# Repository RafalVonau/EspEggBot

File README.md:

# EggBot on ESP8266

## Info

This repository contains the software for my ESP8266 based EggBot.
An [EggBot](https://egg-bot.com/) is a machine for drawing on eggs. I built an eggbot from 3d printed parts from the [thingiverse](https://www.thingiverse.com/thing:3431363) website. 
I'm using an D1 mini(ESP8266) for controlling the steppers and the servo. 

The project is based on:
- [EggDuino](https://github.com/schlion/EggDuino) - some code ported to ESP8266
- [EggBot Inkscape plugin](http://wiki.evilmadscientist.com/Installing_software) - I modified the plugin to automatically detect the USB to UART converter present on the D1 mini board and in case it fails to detect the USB converter, try to connect via TCP with eggbot.local:2500 address
- [EggEsp](https://github.com/M4GNV5/EggEsp) - svg to gcode parser
- [SvgToGCode](https://github.com/evomotors/SvgToGCode) - svg to gcode parser

Features:
- Implemented Eggbot-Protocol-Version 2.1.0
- Turn-on homing: switch-on position of pen will be taken as reference point.
- No collision-detection!!
- Supported Servos: standard analog mini servos like TG9e, SG90, ES08MA, HXT900, etc.
- Taking svgs directly (over www) -> no need for external software.
- Inkscape plugin (commands over serial port or TCP socket on port 2500).

The test project was built on D1 mini board connected to PC computer over USB as /dev/ttyUSB0 under Linux.
Uncomment and modify Wifi client settings in secrets.h file:
* #define WIFI_SSID                "EggBot"
* #define WIFI_PASS                "EggBotPass"

# Parts needed:
* D1 mini (ESP8266),
* DC/DC converter 12V to 5V,
* DC/DC converter 5V to 3.3V,
* 2 x TMC2208/A4988/equivalent,
* 2 x Stepper mottor Nema 17
* Servo SG90/equivalent
* 3D printed and mechanical parts from [thingiverse](https://www.thingiverse.com/thing:3431363)
* wires
* connectors

# D1 mini CONNECTIONS
* STEP1(EGG)- GPIO14 (D5)
* DIR1(EGG) - GPIO13 (D7)
* STEP2(ARM)- GPIO5  (D1)
* DIR2(ARM) - GPIO4  (D2)
* MOTTOR EN - GPIO2  (D4)
* SERVO     - GPIO12 (D6)
* BUTTON    - GPIO0  (D3)

# Wiring

## Building

The project uses platformio build environment. 
[PlatformIO](https://platformio.org/) - Professional collaborative platform for embedded development.

* install PlatformIO
* enter project directory (esp8266_firmware)
* connect Webmos D1 mini board to PC computer over USB cable.
* type in terminal:
  platformio run -t upload

You can also use IDE to build this project on Linux/Windows/Mac. My fvorite ones:
* [Code](https://code.visualstudio.com/) 
* [Atom](https://atom.io/)

## Inkscape plugin installation

Installation:
1. Install inkscape version 0.94
2. Copy inkscape_plugin subdirectories to inkscape user folder:
* On Linux   (~/.config/inkscape/),
* On Windows (c:\Users\[UserName]\AppData\Roaming\inkscape\)

Enjoy :-)

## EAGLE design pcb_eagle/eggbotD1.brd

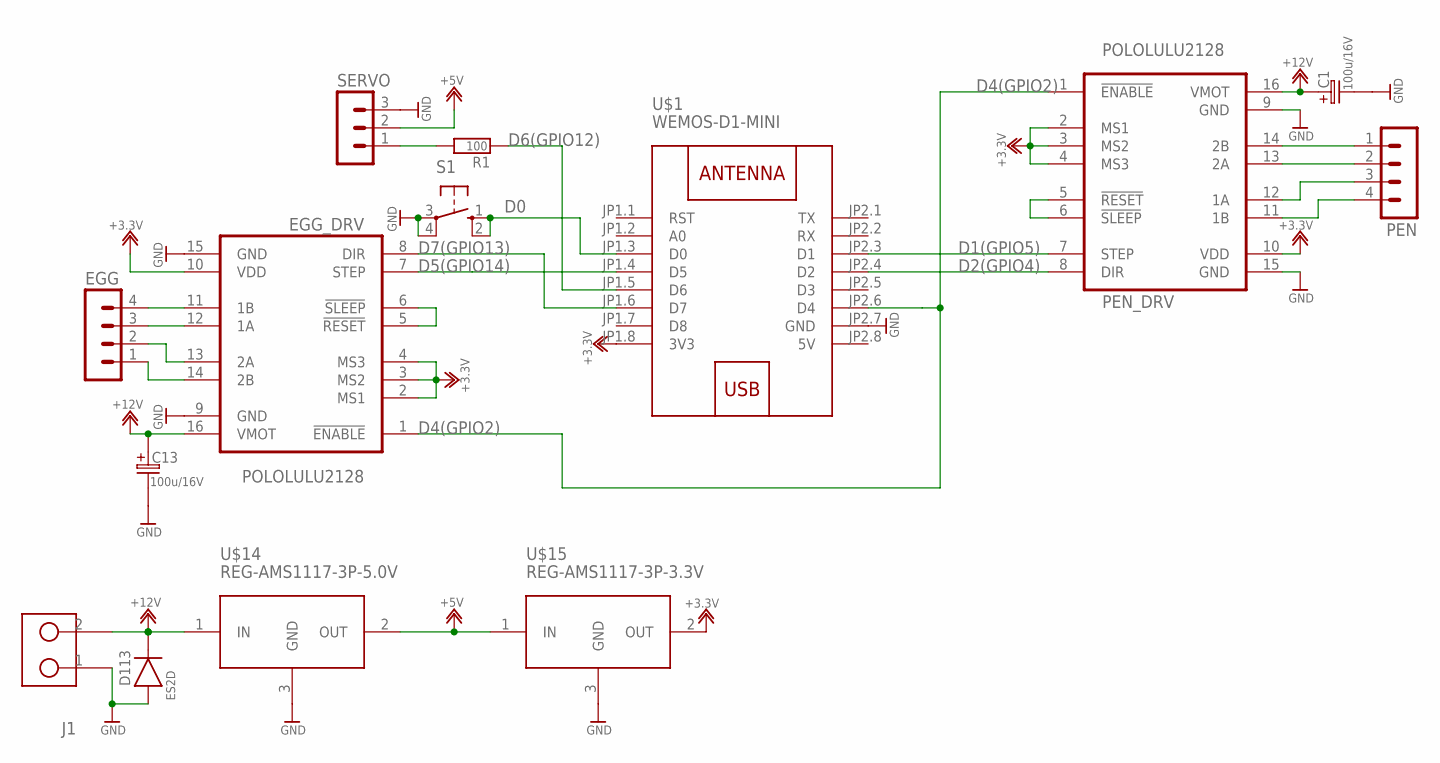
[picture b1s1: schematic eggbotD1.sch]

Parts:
C1, C13: 100u/16V; ES-3,5/8
D113: ES2D; SMB
EGG: MA04-1
EGG_DRV: POLOLULU2128
J1: GMKDS-2; GMKDS1,5
PEN: MA04-1
PEN_DRV: POLOLULU2128
R1: 100; 0805
S1: 10-XX; B3F-10XX
SERVO: MA03-1
U$1: WEMOS-D1-MINI
U$14: REG-AMS1117-3P-5.0V; REG-AMS1117-3P
U$15: REG-AMS1117-3P-3.3V; REG-AMS1117-3P

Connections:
5V: U$1.JP2.8 (5V)
+3.3V: EGG_DRV.2 (MS1), EGG_DRV.3 (MS2), EGG_DRV.4 (MS3), EGG_DRV.10 (VDD), PEN_DRV.2 (MS1), PEN_DRV.3 (MS2), PEN_DRV.4 (MS3), PEN_DRV.10 (VDD), U$1.JP1.8 (3V3), U$15.2 (OUT)
+5V: SERVO.2, U$14.2 (OUT), U$15.1 (IN)
+12V: C1.1, C13.1, D113.2 (K), EGG_DRV.16 (VMOT), J1.2, PEN_DRV.16 (VMOT), U$14.1 (IN)
D0: S1.1 (S), S1.2 (S1), U$1.JP1.3 (D0)
D1(GPIO5): PEN_DRV.7 (STEP), U$1.JP2.3 (D1)
D2(GPIO4): PEN_DRV.8 (DIR), U$1.JP2.4 (D2)
D4(GPIO2): EGG_DRV.1 (!ENABLE), PEN_DRV.1 (!ENABLE), U$1.JP2.6 (D4)
D5(GPIO14): EGG_DRV.7 (STEP), U$1.JP1.4 (D5)
D6(GPIO12): R1.1, U$1.JP1.5 (D6)
D7(GPIO13): EGG_DRV.8 (DIR), U$1.JP1.6 (D7)
GND: C1.2, C13.2, D113.1 (A), EGG_DRV.9 (GND), EGG_DRV.15 (GND), J1.1, PEN_DRV.9 (GND), PEN_DRV.15 (GND), S1.3, S1.4 (P1), SERVO.3, U$1.JP2.7 (GND), U$14.3 (GND), U$15.3 (GND)
unnamed: EGG_DRV.5 (!RESET), EGG_DRV.6 (!SLEEP)
unnamed: PEN_DRV.5 (!RESET), PEN_DRV.6 (!SLEEP)
unnamed: R1.2, SERVO.1
unnamed: PEN.1, PEN_DRV.14 (2B)
unnamed: PEN.2, PEN_DRV.13 (2A)
unnamed: PEN.3, PEN_DRV.12 (1A)
unnamed: PEN.4, PEN_DRV.11 (1B)
unnamed: EGG.4, EGG_DRV.11 (1B)
unnamed: EGG.3, EGG_DRV.12 (1A)
unnamed: EGG.2, EGG_DRV.13 (2A)
unnamed: EGG.1, EGG_DRV.14 (2B)

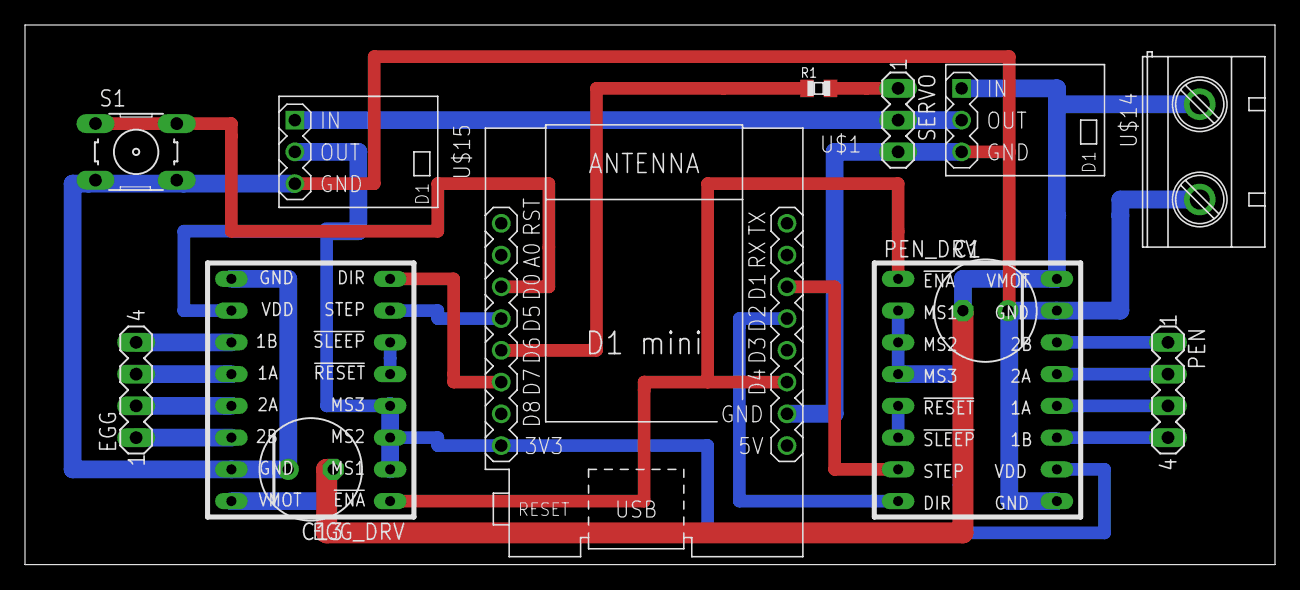
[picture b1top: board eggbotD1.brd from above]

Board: 2 copper layers, 100.0 x 43.2 mm, 14 parts (1 on the bottom side), 22 nets.

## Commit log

2021-04-14 Initial import
2021-04-14 fixups
2021-04-14 WWW - roll over to draw multiple layers
2021-04-14 ABS move support started
2021-04-14 New www (svg to gcode in java script)
2021-04-14 Direction fixup

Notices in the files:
parts and their libraries:
diy-modules: Released under the Creative Commons Attribution 4.0 International License: http://creativecommons.org/licenses/by/4.0
